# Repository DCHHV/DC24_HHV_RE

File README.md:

# DC24_HHV_RE_Challenge
DC24 Hardware Hacking Village Reverse Engineering Challenge

This repo contains all of the sources, eagle files, and gerbers for the
DEF CON 24 Hardware Hacking Village Reverse Engineering challenge.

Do not go any further than this if you wish to not see spoilers.  The eagle
.brd file can be submitted to OSHPark directly if you wish to re-create the 
challenge.

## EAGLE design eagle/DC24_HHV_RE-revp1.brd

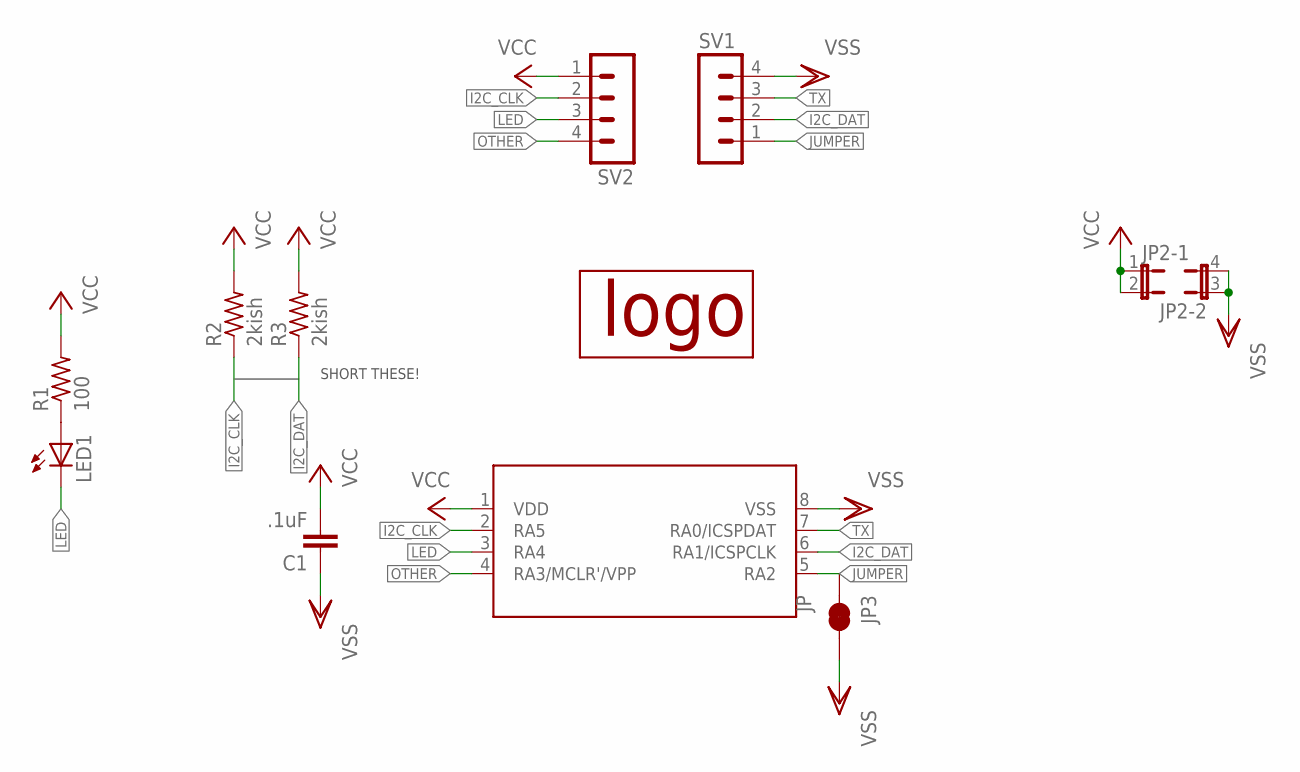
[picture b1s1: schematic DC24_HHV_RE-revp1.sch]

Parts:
C1: .1uF; C050-024X044
JP2: JP2QE; JP2Q
JP3: JP; PAD-JUMPER-2-NC_BY_TRACE_YES_SILK
LED1: LED5MM
R1: 100; 0204/7
R2, R3: 2kish; 0204/7
SV1, SV2: MA04-1
U1: PIC12F1571; DIL8
U$1: KBELOGO-SILK

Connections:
I2C_CLK: R2.1, SV2.2, U1.2 (RA5)
I2C_DAT: R3.1, SV1.2, U1.6 (RA1/ICSPCLK)
JUMPER: JP3.1, SV1.1, U1.5 (RA2)
LED: LED1.K (C), SV2.3, U1.3 (RA4)
unnamed: LED1.A, R1.1
OTHER: SV2.4, U1.4 (RA3/MCLR'/VPP)
TX: SV1.3, U1.7 (RA0/ICSPDAT)
VCC: C1.2, JP2.1, JP2.2, R1.2, R2.2, R3.2, SV2.1, U1.1 (VDD)
VSS: C1.1, JP2.3 (1), JP2.4 (2), JP3.2, SV1.4, U1.8 (VSS)

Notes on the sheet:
SHORT THESE!

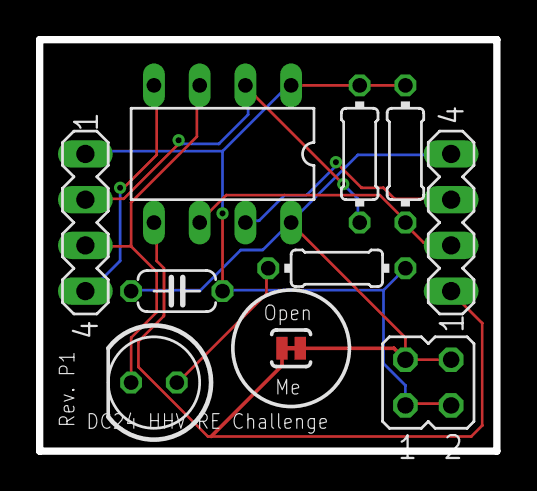
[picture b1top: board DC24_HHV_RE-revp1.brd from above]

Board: 2 copper layers, 25.4 x 22.9 mm, 11 parts (0 on the bottom side), 9 nets.

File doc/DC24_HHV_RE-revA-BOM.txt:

Qty Value        Device                   Package                           Parts    Description
1                JP2QE                    JP2Q                              JP2      JUMPER 2x2
1                LED5MM                   LED5MM                            LED1     LED
2                MA04-1                   MA04-1                            SV1, SV2 PIN HEADER 1x4
1   .1uF         C-EU050-024X044          C050-024X044                      C1       CAPACITOR ALUM.
1   100          R-US_0204/7              0204/7                            R1       RESISTOR
2   2k           R-US_0204/7              0204/7                            R2, R3   RESISTOR
1   PIC12F1571   PIC12F1571               DIL8                              U1

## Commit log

2016-07-22 Initial commit P1 PCB completed
2016-07-22 Initial commit of MPLAB project Initial untested code
2016-07-22 Updated gerbv layer order
2016-07-22 UART and I2C now working Main code flow is correct, final testing and tweaking needed
2016-07-22 Added obfuscator program to output the obfuscation used in ROM for strings
2016-07-22 Added kitlabels and HHV instructions/entry form
2016-07-22 Re-wired fake traces to be one being looped trace not connected to anything real Created new gerbers, final rev A Added DRC file to project
2016-07-22 Added note to schematic about handling jumper pad in Rev A
2016-07-22 Added note on schematic about running a short between I2C clk and dat in Rev A
2016-07-22 No longer open CAM window on startup
2016-07-22 Added rev A PCB eagle files, default to open these on project open Removed a lot of information from silkscreen on PCB
2016-07-22 Updated hex file to latest production
2016-07-22 Rearranged startup to eliminate the UART hiccup Set up proper byte offset for ROM puzzle
2016-07-22 Updated comments Cleaned up I2C timing so clock is 50% duty
2016-07-22 Updated documentation in comments
2016-07-22 Added hex file, known good and working
2016-07-22 Proposed final of rev A PCB Added CAM file and gerber files
2016-07-24 Fixed typo
2016-07-24 Added hex file and updated README
2016-08-09 Updated README for post DEF CON information
2016-08-10 Created writeup of the challenge
2018-04-10 Added BOM
2018-04-10 Added CAM file for OSHPark as well as gerbers for OSHPark processing
2018-04-26 Updated gitignore for CAM output files Updated gerber output for OSHPark to include *place outlines Added gerbv project file for OSHPark files

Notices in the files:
parts and their libraries:
SparkFun-Passives: Licensing: Creative Commons ShareAlike 4.0 International - https://creativecommons.org/licenses/by-sa/4.0
